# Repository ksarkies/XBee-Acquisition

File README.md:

XBee Data Acquisition
---------------------

This project develops a remote data collection board, primarily aimed at a
specific water flow meter. The board communicates collected counts of optical
transitions from a rotating slotted wheel, over an XBee network to a master
processing point. The remote unit includes a bootloader for remote upload of
new firmware.

The challenge with this project is to reduce power consumption to a minimum
to extend the life of the batteries, which may be difficult to access for
recharge in practice.

In addition to the board design and firmware, a number of tools are provided
to manage the network and collect data using Linux based hardware. These include
an acquisition coordination process that is intended to run on a small headless
Linux box such as a Raspberry Pi or BeagleBone. This manages the network and
connects to a user interface program running either on the same machine or
at another location. It uses a TCP/IP sockets interface that will allow remote
connections over the Internet.

A number of test and debug firmwares are available as well as schematics for
prototyping boards used as test nodes.

Subdirectories:

* **Documentation**:           A set of documents relevant to design and implementation.

* **gEDA-XBee-Test**:          Schematics for prototype boards for testing purposes.

* **Kicad-Main**:              Schematic and PCB for watermeter unit main board.

* **Kicad-Mounts**:            Schematic and PCB for XBee and LED mount boards.

* **watermeter-test**:         Firmware for the remote unit ATTiny481, in C, for use
 with flow bench testing over a serial interface. XBee is not used.

* **XBee-acqcontrol**:         Control software for the coordinator; in C++.

* **XBee-bootloader-M168**:    Bootloader for a remote unit with ATMega168.

* **XBee-experimental-T4313**: Bootloader for a remote unit with ATTiny4313.

* **XBee-firmware**:           Firmware for the remote unit ATTiny481, in C.

* **XBee-firmware-NARTOS**:    Firmware for remote unit ATTiny481 using the NARTOS
scheduler.

* **XBee-GUI**:                Linux PC based GUI for network control; C++ and QT.

* **XBee-node-example-M168**:  Example to send dummy message via XBee for testing.

* **XBee-utility**:            Some tools for direct interaction with XBee over a
serial interface.

K. Sarkies
29 January 2016

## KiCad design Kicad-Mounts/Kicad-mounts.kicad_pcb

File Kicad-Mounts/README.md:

XBee Data Acquisition XBee/LED Mountings
----------------------------------------

Refer to [Kicad-setup](https://github.com/ksarkies/XBee-Acquisition/blob/master/Documentation/Kicad-Setup.md) in the Documentation directory for usage information.

TDB: At this time the PCB has missing footprints.

This board provides a mounting PCB for the LED and a mounting PCB for the XBee
with matching connector for right-angle mount to the main PCB.

An XBee footprint was taken from RF_OEM_PARTS.lib and footprints.mod in Ian
McInerney's library (https://github.com/imciner2/KiCad-Libraries)
The legacy footprint has been modified to the newer kicad_mod format and solder
mask has been added to the pads.

The LED mount provides for two LEDs VSMY2850 and SFH4056 reverse mounted (under
the board and facing through a cutout) and a top mounted LED SFH4258.

Other symbols and footprints are provided by KiCad developers.

27 November 2014: Flip XBee over, adjust XBee footprint, reduce size the of the
                  two boards, interchange Rx and Tx.

A separate regulated supply was added to provide 3.3V power for the XBee as the
XBee can pull a relatively heavy current pulse on transmission.

K. Sarkies
19 February 2016

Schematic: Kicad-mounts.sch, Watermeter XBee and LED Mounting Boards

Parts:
C1: 0.47uF; SMD-0603_c
C2: 0.1uF; SMD-0603_c
C3: 10uF; SMD-1206_Pol
D1: SFH4056
P3: CONN_6X2; pin_header_2mm_2x6
P6: CONN_3; SIL-3
U2: TPS77033; SOT-23-5

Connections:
/Association: P3.10; also elsewhere on the board
/Bootloader: P3.3; also elsewhere on the board
/Commissioning: P3.1; also elsewhere on the board
/On/Sleep: P3.9; also elsewhere on the board
/Reset: P3.5; also elsewhere on the board
/Rx: P3.7; also elsewhere on the board
/Sleep_Rq: P3.8; also elsewhere on the board
/Tx: P3.12; also elsewhere on the board
/V3: C2.1, C3.1, U2.5 (OUT); also elsewhere on the board
/VBatt: P3.4; also elsewhere on the board
/XBee-Reset: P3.6; also elsewhere on the board
GND: C1.2, C2.2, C3.2, P3.11, U2.2 (GND), U2.3 (~EN~); also elsewhere on the board
unnamed: D1.1, P6.2, P6.3
unnamed: D1.2, P6.1
VCC: C1.1, P3.2, U2.1 (IN)

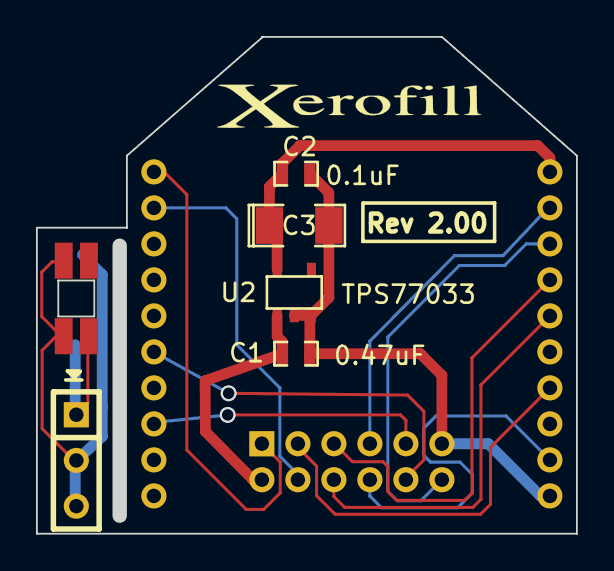
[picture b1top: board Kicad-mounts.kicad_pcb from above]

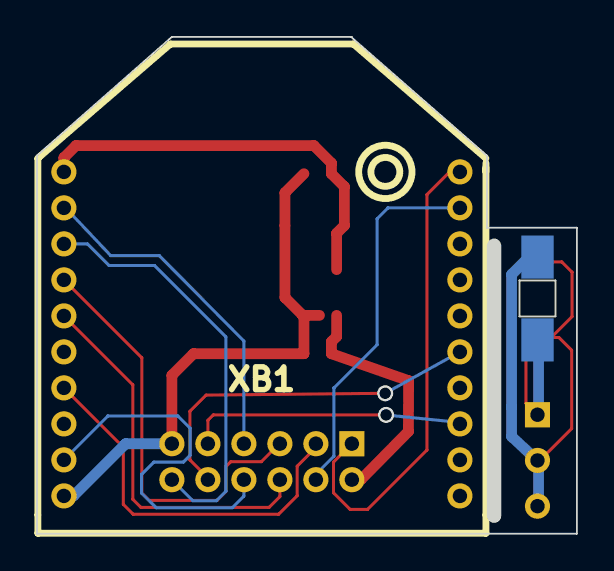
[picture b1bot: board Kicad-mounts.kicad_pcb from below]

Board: 2 copper layers, 30.0 x 27.6 mm, 8 parts (2 on the bottom side), 15 nets.

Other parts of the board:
XB1: XBEE; XBee

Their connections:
/Association: XB1.15; also elsewhere on the board
/Bootloader: XB1.7; also elsewhere on the board
/Commissioning: XB1.20; also elsewhere on the board
/On/Sleep: XB1.13; also elsewhere on the board
/Reset: XB1.4; also elsewhere on the board
/Rx: XB1.2; also elsewhere on the board
/Sleep_Rq: XB1.9; also elsewhere on the board
/Tx: XB1.3; also elsewhere on the board
/V3: XB1.1; also elsewhere on the board
/VBatt: XB1.19; also elsewhere on the board
/XBee-Reset: XB1.5; also elsewhere on the board
GND: XB1.10; also elsewhere on the board

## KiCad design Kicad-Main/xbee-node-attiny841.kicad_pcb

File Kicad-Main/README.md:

XBee Data Acquisition PCB
-------------------------

Refer to [Kicad-setup](https://github.com/ksarkies/XBee-Acquisition/blob/master/Documentation/Kicad-Setup.md) in the Documentation directory for usage information.

PCB for a remote unit, including XBee with battery monitor and photodiode
counter. A major requirement for this circuit is ultra-low power to allow the
selected batteries to last for over a year.

The PCB is intended to fit inside a cylindrical watermeter with the batteries.
Due to space constraints the XBee is mounted on a separate board that sits at
right angles to the PCB. The XBee connects to an external aerial through an RF
cable. For measurement of battery voltage, a switched divider circuit is
provided for the case that the batteries provide a higher voltage than the
circuit power supply (which is sourced via a 3.3V voltage regulator). The LED is
mounted on a separate board that will straddle an interrupter wheel for counting
revolutions of the meter.

The board has a 12-pin debug connector for testing purposes:

1. Battery power or board power (if a battery is present take extreme care not
to short or connect any other power source).
2. Count signal from board comparator.
3. Reset for microcontroller.
4. MOSI microcontroller programming pin.
5. SCK microcontroller programming pin.
6. MISO microcontroller programming pin.
7. Tx from microcontroller to XBee Rx (monitor this only unless XBee is removed).
8. Rx to microcontroller from XBee Tx (monitor this only unless XBee is removed).
9. Association Signal from XBee. Blinks at 2Hz when connected to the network.
10. On/Sleep (high if XBee is awake, low if asleep).
11. Commissioning input to XBee, requiring a pushbutton to ground.
12. Ground.

The microcontroller has the following I/O pin allocations:

* PA0 (in) XBee Asleep (inv)
* PA1 (out) Tx to XBee
* PA2 (in) Rx to XBee
* PA3 (out) Sleep Request
* PA4 (in) SCK
* PA5 (in) MISO
* PA6 (out) MOSI
* PA7 (out) Battery Monitor Control
* PB0 (in) Bootloader Enable
* PB1 (in) Board Digital Input
* PB2 (out) XBee Reset (inv)

The battery monitor voltage is passed directly to the XBee as the ATTiny841 has
insufficient pins.

The TPS77033 symbol from KB1LQC.lib at Rochester Institute of technology
(http://edge.rit.edu/edge/P13271/public/KiCad/Libraries).

A photodiode symbol was taken from
(http://vkoeppel.free.fr/files/diy/kicad_diy_libraries.zip)

Other symbols and footprints are custom or are provided by KiCad developers.

The provided Photodiode.pretty footprint library should contain all necessary
footprints. Copy any legacy footprints into the modules directory, and any
external footprints into Photodiode.pretty to avoid problems of obsolescence. In
CvPcb go to "Library Tables", then select the tab "Project Specific Libraries".
Append a new entry, add the library path (including the name of the .mod file),
choosing "Legacy" for the plugin type. The nickname will then appear in the main
listing of CvPcb and the library footprints should appear. If a mistake is made,
no footprints will show, but no error message will be given until CvPcb is
restarted.

A custom footprint S1133 is provided for the S1133 photodiode. This has a
truncated circular form 8mm diameter with 6mm across the truncation, and through
hole pins. In CvPcb append a new KiCad entry and add the library path to the
.pretty directory (not the file, which is a single footprint). Also included
are some 2mm pin spacing header footprints.

The production version of the board has a custom footprint for the debug
connector to allow the option of using an SMD form. Also the photodiode is now
a BPW34 which can be either SMD or through hole mounted below the board, or a
reverse form mounted on top of the board over the square hole. The latter choice
avoids possible interference with mechanical parts in the space under the board.

The [node test firmware](https://github.com/ksarkies/XBee-Acquisition/tree/master/Development/XBee-node-test) is provided for test transmissions.

The [firmware](https://github.com/ksarkies/XBee-Acquisition/tree/master/XBee-firmware) is provided for full protocol transmissions.

Firmware must be compiled for MCU=attiny841 or whichever processor is used.

The firmware README provides instructions for setting up the XBee configuration.

* 27 November 2014: Add missing ground points. Correct error in battery voltage
  circuit.
* 24 February 2016: Changed position of connectors to avoid housing structures.
* 11 April 2016: Production version with additional XBee signals brought out to
  the debug connector which is now 12 pin.
* 12 February 2017: Corrections to the battery monitor circuit.

K. Sarkies
11 April 2016

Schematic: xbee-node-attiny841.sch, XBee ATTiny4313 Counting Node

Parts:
C1, C2, C6, C7, C8, C9: 0.1uF; SM0603_Capa
C3: 10uF; SM1206POL
C4: 0.47uF; SM0603_Capa
D1: SFH4056; LED-Mount
D2: BPW-34 S (E9087); BPW34
L1: 100nH; R_0805
P2: XBee Adaptor; pin_header_2mm_2x6
P3: Debug Adaptor; pin_smd_header_2mm_2x6
P7, P8, P9, P10, P11: CONN_1; SIL-1
P12, P13, P14, P15, P16, P17, P18, P19, P20: CONN_1; THROUGHVIA
Q1: BSS84; SOT23GDS
Q2: MMBT3904; SOT23EBC
Q3: 2N7002; SOT23GDS
R1, R6: 10K; SM0603_Resistor
R2: 33K; SM0603_Resistor
R3: 270K; SM0603_Resistor
R4, R5, R9: 1M; SM0603_Resistor
R7: 15K; SM0603_Resistor
R8: 4.7K; SM0603_Resistor
U1: ATTINY841; ATTINY841-SSU
U2: MAX952ESA; SO8N
U3: TPS77033; SOT23-5

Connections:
/Association: P2.10, P3.9
/Battery: C4.1, P2.2, P3.1, P7.1, P8.1, P9.1, Q1.S, R6.1, U3.1 (IN)
/Bootloader: P2.3, U1.2 ((PCINT8/CLKI/XTAL1)PB0)
/Commissioning: P2.1, P3.12
/Count: P3.2, R4.2, U1.3 ((PCINT9/XTAL2)PB1), U2.7
/MISO: P3.6, U1.8 ((PCINT5/DO/MISO/OC1B/ADC5)PA5)
/MOSI: P3.4, U1.7 ((PCINT6/SDA/DI/MOSI/OC1A/ADC6)PA6)
/On/Sleep: P2.9, P3.10, U1.13 ((PCINT0/AREF/ADC0)PA0)
/PowerControl: Q3.G, R9.2, U1.6 ((PCINT7/ICP/OC0B/ADC7)PA7)
/Reset: C1.1, P2.5, P3.3, R1.1, U1.4 ((PCINT11/dW/~RESET~)PB3)
/Rx: P2.7, P3.8, U1.11 ((PCINT2/AIN1/ADC2)PA2)
/SCK: P3.5, U1.9 ((PCINT4/USCK/SCL/T1/ADC4)PA4)
/Sleep-Rq: P2.8, R5.2, U1.10 ((PCINT3/T0/ADC3)PA3)
/Tx: P2.12, P3.7, U1.12 ((PCINT1/AIN0/ADC1)PA1)
/VBatt: P2.4, R7.2, R8.1
/VDDA: C6.1, C9.1, D2.2 (K), L1.1, R2.1, R3.1, U2.8 (V+)
/Xbee-Reset: P2.6, U1.5 ((PCINT10/CKOUT/OC0A/INT0)PB2)
GND: C1.2, C2.2, C3.2, C4.2, C6.2, C7.2, C8.2, C9.2, D1.2 (K), P2.11, P3.11, P10.1, P11.1, P12.1, P13.1, P14.1, P15.1, P16.1, P17.1, P18.1, P19.1, P20.1, Q2.1 (E), Q3.S, R5.1, R8.2, R9.1, U1.14 (GND), U2.2 (-), U2.3 (+), U2.4 (V-), U3.2 (GND), U3.3 (~EN~); also elsewhere on the board
unnamed: D1.1 (A), R2.2
unnamed: D2.1 (A), Q2.2 (B)
unnamed: Q1.D, R7.1
unnamed: Q1.G, Q3.D, R6.2
unnamed: Q2.3 (C), R3.2, R4.1, U2.5 (+)
VDD: C2.1, C3.1, C7.1, C8.1, L1.2, R1.2, U1.1 (VCC), U3.5 (OUT)

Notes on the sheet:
Battery Connections
Vias
XBee Connectors
Debug Connector

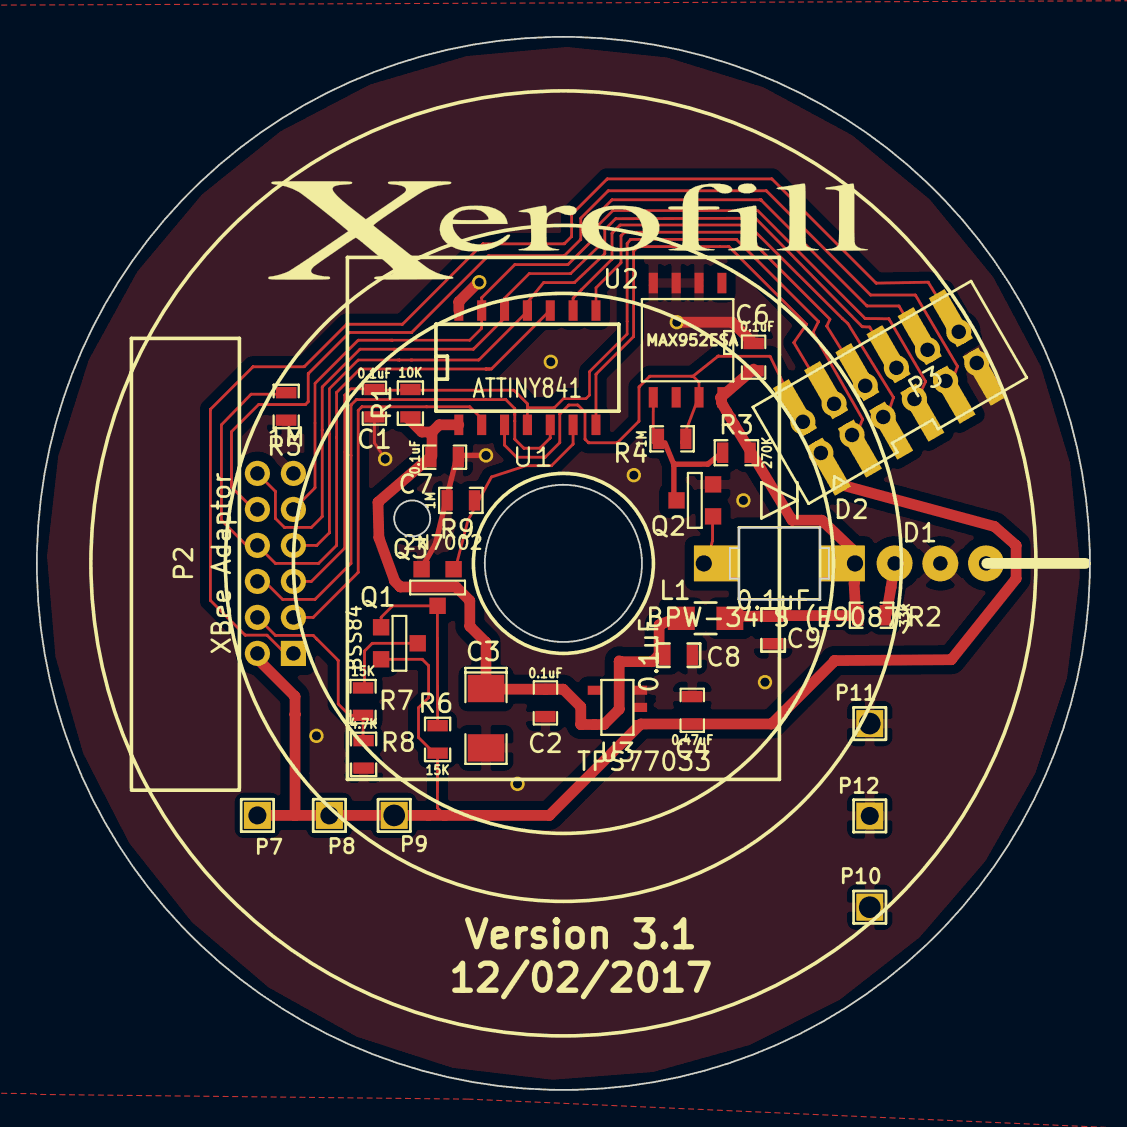
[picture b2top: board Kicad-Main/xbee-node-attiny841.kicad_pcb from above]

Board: 2 copper layers, 58.5 x 58.5 mm, 44 parts (0 on the bottom side), 24 nets.

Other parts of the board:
P12#2: CONN_1; THROUGHVIA
Ref**: Val**; THROUGHVIA

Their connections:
GND: P12#2.1, Ref**.1; also elsewhere on the board

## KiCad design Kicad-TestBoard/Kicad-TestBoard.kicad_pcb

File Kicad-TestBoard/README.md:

XBee Data Acquisition TestBoard
-------------------------------

This board is for use with the watermeter assembly. It provides power, an
interface to an AVR programmer, and a serial interface to an external PC.
LEDs are provided for association indication, on/sleep and commissioning
signals from the XBee. A reset switch for the AVR is provided.

There are pins for a CRO to view the count signal from the assembly.

Jumpers are provided as follows:

* Disconnect external serial line. This **must** be left open when the XBee is
present in the watermeter assembly otherwise both serial sources are
mutually interfering and the XBee could be damaged.

* Disconnect power to watermeter assembly. This **must** be left open when the
watermeter assembly has an on-board battery. With Lithium batteries there is a
strong chance of explosion or fire if an external voltage source is connected.

K. Sarkies
19 January 2017

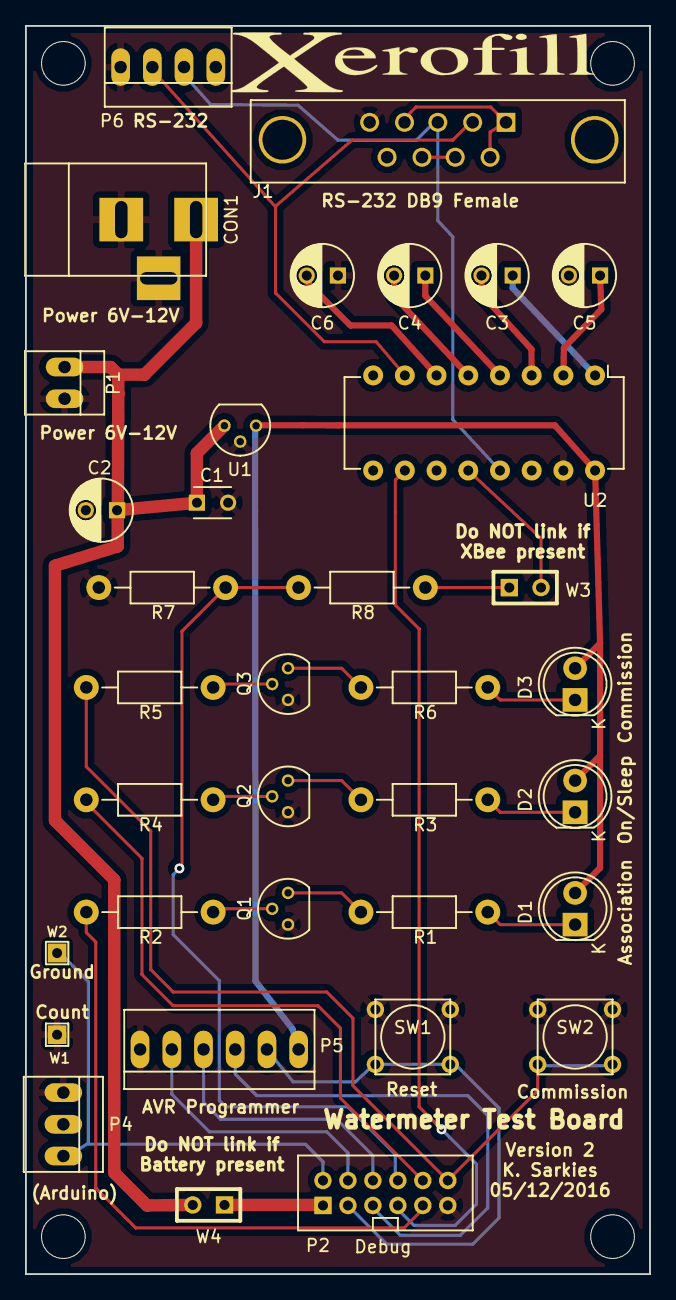
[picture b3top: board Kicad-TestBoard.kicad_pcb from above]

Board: 2 copper layers, 50.0 x 100.0 mm, 35 parts (0 on the bottom side), 35 nets.

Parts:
C1: 0.1uF; C_Disc_D3_P2.5
C2: 10uF; C_Radial_D5_L11_P2.5
C3, C4, C5, C6: 1uF; C_Radial_D5_L11_P2.5
CON1: Power 6V-12V; BARREL_JACK
D1: Yellow LED; LED-5MM
D2: Green LED; LED-5MM
D3: Red LED; LED-5MM
J1: DB9 RS-232 Female; DB9FD
P1: Power 6V-12V; PINHEAD1-2
P2: Debug; pin_header_2mm_2x6_shrouded
P4: Arduino; PINHEAD1-3
P5: AVR Programmer; PINHEAD1-6
P6: RS-232; PINHEAD1-4
Q1: Association; TO-92_Molded_Narrow
Q2: On_Sleep; TO-92_Molded_Narrow
Q3: Commissioning; TO-92_Molded_Narrow
R1, R3, R6, R8: 470; Resistor_Horizontal_RM10mm
R2, R4, R5: 10K; Resistor_Horizontal_RM10mm
R7: 1K; Resistor_Horizontal_RM10mm
SW1: Reset; SW_PUSH_TINY
SW2: Commissioning; SW_PUSH_TINY
U1: 78L05; TO-92_78L05
U2: MAX232; DIP-16_W7.62mm
W1, W2: TEST_1P; SIL-1
W3, W4: Jumper; SIL-2

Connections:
/Battery: P2.1, W4.1
/Commissioning: P2.12, R5.2, SW2.2
/Count: P2.2, P4.3, W2.1
/MISO: P2.6, P5.3
/MOSI: P2.4, P5.2
/On_Sleep: P2.10, R4.2
/Reset: P2.3, P5.5, SW1.2
/Rx: P2.8, R7.1, R8.2
/SCK: P2.5, P5.4
/Tx: P2.7, U2.10
Earth: C1.2, C2.2, C5.2, C6.1, CON1.2, CON1.3, J1.5, P1.2, P2.11, P4.1, P5.1, P6.4, Q1.1, Q2.1, Q3.1, R7.2, SW1.1, SW2.1, U1.GND, U2.15, W1.1
unnamed: C1.1, C2.1, CON1.1, P1.1, U1.VI, W4.2
unnamed: C3.1, U2.1
unnamed: C3.2, U2.3
unnamed: C4.1, U2.4
unnamed: C4.2, U2.5
unnamed: C5.1, U2.2
unnamed: C6.2, U2.6
unnamed: D1.1, R1.1
unnamed: D2.1, R3.1
unnamed: D3.1, R6.1
unnamed: J1.1, J1.4, J1.6
unnamed: J1.2, P6.3, U2.7
unnamed: J1.3, P6.2, U2.13
unnamed: J1.7, J1.8
unnamed: P2.9, R2.2
unnamed: Q1.2, R2.1
unnamed: Q1.3, R1.2
unnamed: Q2.2, R4.1
unnamed: Q2.3, R3.2
unnamed: Q3.2, R5.1
unnamed: Q3.3, R6.2
unnamed: R8.1, W3.1
unnamed: U2.12, W3.2
VCC: D1.2, D2.2, D3.2, P5.6, U1.VO, U2.16

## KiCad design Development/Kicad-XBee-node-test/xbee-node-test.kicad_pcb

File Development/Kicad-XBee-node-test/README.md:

XBee Node Test Board PCB
------------------------

This is a small test board PCB.

This includes an XBee with ATMega48 and with an analogue battery monitor,
digital counter input and a second analogue input. It takes an input 5-14V power
and produces 3.3V power for the electronics.

The microcontroller has the following I/O pin allocations:

* PB2 (in) Bootloader Enable taken from XBee DIO11 pin..
* PB3 (out) Programming SPI interface MOSI.
* PB4 (in) Programming SPI interface MISO.
* PB5 (in) Programming SPI interface SCK.
* PC0 (in) Board Analogue Input also taken to XBee AD2 pin.
* PC1 (in) Battery Monitor Analogue Input also taken to XBee AD1 pin.
* PC3 (out) Debug Signal LED.
* PC4 (out) Microcontroller Activity LED.
* PC5 (out) Battery Monitor Control.
* PD2 (in) taken from XBee CTS pin.
* PD3 (out) taken to XBee RTS pin.
* PD4 (in) Board Digital Input.
* PD5 (out) XBee Sleep Request.
* PD6 (in) XBee On/Sleep.
* PD7 (out) XBee Reset (inv) taken to the XBee reset pin.
* Microcontroller Reset taken from XBee DIO12 pin.

Four LEDs are provided:
* Red       Power.
* Green     PC4 Microcontroller Activity (test port) from ATMega48.
* Blue      Debug Signal.
* Yellow    Association status from XBee.

The [node test firmware](https://github.com/ksarkies/XBee-Acquisition/tree/master/Development/XBee-node-test) is provided for test transmissions.

The [firmware](https://github.com/ksarkies/XBee-Acquisition/tree/master/XBee-firmware) is provided for full protocol transmissions.

Firmware must be compiled for MCU=atmega48 or whichever processor is used.

The firmware README provides instructions for setting up the XBee configuration.

K. Sarkies
2 March 2017

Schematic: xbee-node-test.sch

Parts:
C1, C2, C3, C4, C5: 0.1uF; SM0603_Capa
C6, C7: 10uF; SM1206POL
C8: 0.47uF; SM0603_Capa
D1: LM336-2.5V; TO-92_LM336
D2: Test; LED-5MM
D3, D5: 1N4148; D_0603
D4: Associate; LED-5MM
D6: Debug; LED-5MM
D7: Power; LED-5MM
D8: CUS520; D_SOD-323_HandSoldering
IC1: ATMEGA48-P; DIP-28
L1, L2: 100nH; R_0805
P1: Program; PINHEAD1-6
P2: Power 3.7V-12V; PINHEAD1-2
P3: Analogue; PINHEAD1-2
P4: Count; PINHEAD1-2
P5: VRef; SIL-1
P6: GND; SIL-1
Q1: 2N7002; SOT23GDS
Q2: BSS84; SOT23GDS
R1, R9, R11: 10K; SM0603_Resistor
R2: 2.2K; SM0603_Resistor
R3, R4, R5, R6: 220; SM0603_Resistor
R7, R8, R14: 1M; SM0603_Resistor
R10: 1K; SM0603_Resistor
R12: 15K; SM0603_Resistor
R13: 4.7K; SM0603_Resistor
RV1: 100K; Potentiometer_Bourns_3362F
Reset1: Reset; SW_PUSH_TINY
SW2: Commissioning; SW_PUSH_TINY
U1: TPS77033; SOT23-5
W1, W2, W3: Jumper; SIL-2
XB1: XBEE; XBee

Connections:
/ARef: C2.1, D1.2 (+), D3.2 (A), IC1.21 (AREF), P5.1, R2.2
/AVcc: C4.1, IC1.20 (AVCC), L2.1
/Analogue: IC1.23 ((PCINT8/ADC0)PC0), R10.2, R14.1, XB1.18 (AD2/DIO2)
/Associate: W2.2, XB1.15 (AD5/DIO5)
/Battery: D8.2 (A), P2.1, Q2.S, R9.1
/Bootloader: IC1.16 ((PCINT2/OC1B/~SS~)PB2), XB1.7 (PWM1)
/CTS: IC1.4 ((PCINT18/INT0)PD2), XB1.12 (DIO7/~CTS~)
/Commissioning: SW2.1, XB1.20 (AD0/DIO0)
/Counter: IC1.6 ((PCINT20/XCK/T0)PD4), R11.2
/DEBUG: IC1.26 ((PCINT11/ADC3)PC3), R5.2
/MC_Reset: C1.1, IC1.1 ((PCINT14/~RESET~)PC6), P1.5, R1.2, Reset1.1, XB1.4 (D08)
/MISO: IC1.18 ((PCINT4/MISO)PB4), P1.3
/MOSI: IC1.17 ((PCINT3/OC2/MOSI)PB3), P1.2
/On_Sleep: IC1.11 ((PCINT21/OC0B/T1)PD5), XB1.13 (ON/~SLEEP~)
/RTS: IC1.5 ((PCINT19/OC2B/INT1)PD3), XB1.16 (~RTS~/AD6/DIO6)
/RxD: IC1.2 ((PCINT16/RXD)PD0), XB1.2 (DOUT)
/SCK: IC1.19 ((PCINT5/SCK)PB5), P1.4
/Sleep_RQ: IC1.12 ((PCINT22/OC0A/AIN0)PD6), R7.1, XB1.9 (~DI8~/DTR/SLEEP_RQ)
/TEST: IC1.27 ((PCINT12/SDA/ADC4)PC4), R3.2
/TxD: IC1.3 ((PCINT17/TXD)PD1), XB1.3 (DIN/~CONFIG)
/VBAT: IC1.24 ((PCINT9/ADC1)PC1), R12.2, R13.1, XB1.19 (AD1/DIO1)
/VBAT_CTL: IC1.28 ((PCINT13/SCL/ADC5)PC5), Q1.G, R8.1
/Vcc: C3.1, C5.1, IC1.7 (VCC), L1.1, P1.6, R1.1, W1.1, W3.2, XB1.1 (VCC)
/XBee_Reset: IC1.13 ((PCINT23/AIN1)PD7), XB1.5 (~RESET)
GND: C1.2, C2.2, C3.2, C4.2, C5.2, C6.2, C7.2, C8.2, D1.3 (-), D2.1 (K), D4.1 (K), D5.1 (K), D6.1 (K), D7.1 (K), IC1.8 (GND), IC1.22 (GND), P1.1, P2.2, P3.2, P4.2, P6.1, Q1.S, R7.2, R8.2, R13.2, R14.2, Reset1.2, SW2.2, U1.2 (GND), U1.3 (~EN~), XB1.10 (GND)
unnamed: C6.1, L1.2, L2.2, U1.5 (OUT)
unnamed: C7.1, C8.1, D8.1 (K), U1.1 (IN)
unnamed: D1.1 (ADJ), RV1.2
unnamed: D2.2 (A), R3.1
unnamed: D3.1 (K), RV1.3
unnamed: D4.2 (A), R4.1
unnamed: D5.2 (A), RV1.1
unnamed: D6.2 (A), R5.1
unnamed: D7.2 (A), R6.1
unnamed: P3.1, R10.1
unnamed: P4.1, R11.1
unnamed: Q1.D, Q2.G, R9.2
unnamed: Q2.D, R12.1
unnamed: R2.1, W1.2
unnamed: R4.2, W2.1
unnamed: R6.2, W3.1

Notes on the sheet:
XBee Node test Board
31/01/2017

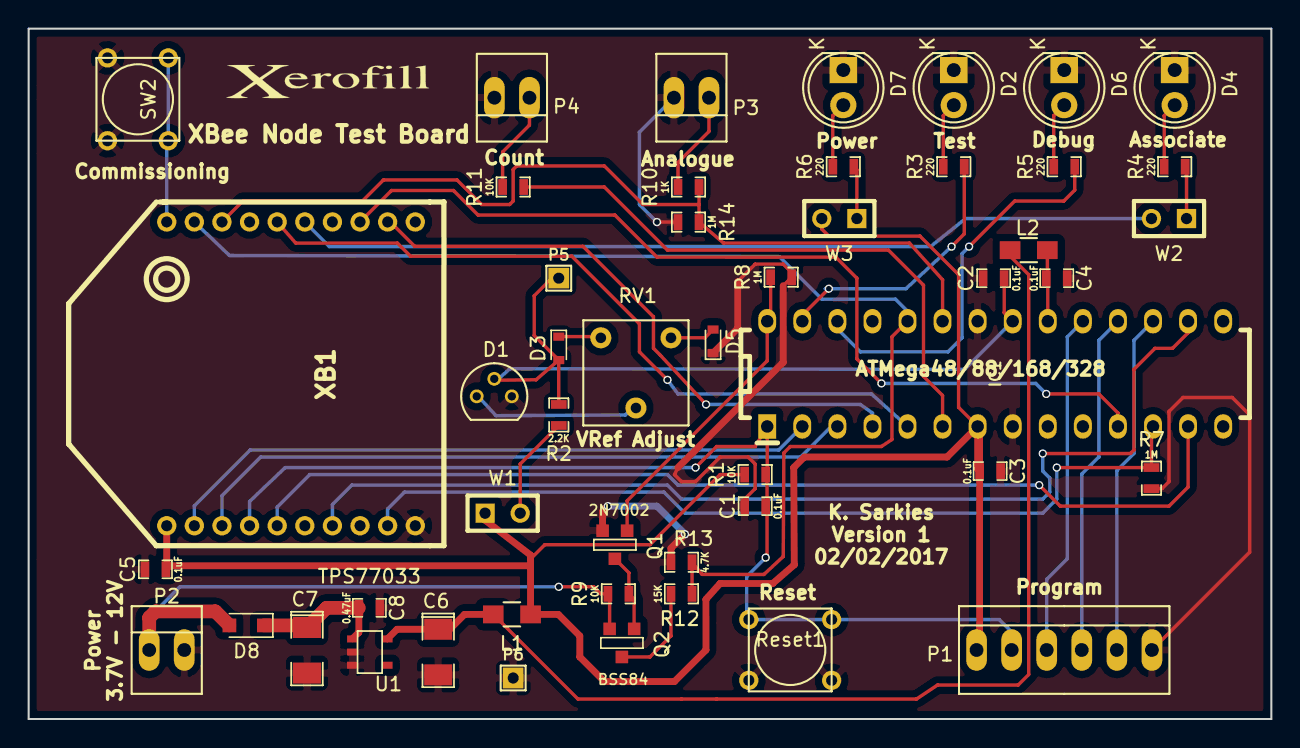
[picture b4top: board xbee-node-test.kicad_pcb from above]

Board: 2 copper layers, 90.0 x 50.0 mm, 49 parts (0 on the bottom side), 41 nets.

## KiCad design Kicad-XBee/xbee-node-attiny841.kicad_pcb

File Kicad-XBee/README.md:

XBee Data Acquisition PCB
-------------------------

PCB for remote unit, including XBee with battery monitor and photodiode
counter. A major requirement for this circuit is ultra-low power to allow the
batteries to last for over a year.

The PCB is intended to fit inside a cylindrical watermeter along with batteries.
Due to space constraints the XBee is mounted on a separate board that sits at
right angles to the PCB. The XBee connects to an external aerial through an RF
cable. For measurement of battery voltage, a switched divider circuit is
provided for the case that the batteries provide a higher voltage than the
circuit power supply which is sourced via a voltage regulator). The LED is
mounted on a separate board that will straddle an interrupter wheel for counting
revolutions of the meter.

XBee and 5x2 connector symbol and footprint is taken from Ian McInerney:
https://github.com/imciner2/KiCad-Libraries RF_OEM_PARTS.lib and footprints.mod

TPS77033 symbol from Rochester Institute of technology:
http://edge.rit.edu/edge/P13271/public/KiCad/Libraries KB1LQC.lib and KB1LQC.mod

The latter is a legacy footprint. Place the file into the modules directory. In
CvPcb go to "Library Tables", then select the tab "Project Specific Libraries".
Append a new entry, add the library path (including the name of the .mod file),
choosing "Legacy" for the plugin type. The nickname will then appear in the main
listing of CvPcb and the library footprints should appear. If a mistake is made,
no footprints will show, but no error message will be given until CvPcb is
restarted.

A custom footprint S1133 is provided for the photodiode. This actually has a
truncated circular form 8mm diameter with 6mm across the truncation, and through
hole pins. In CvPcb append a new KiCad entry and add the library path to the
.pretty directory (not the file, which is a single footprint). Also included
are some 2mm pin spacing header footprints.

K. Sarkies
9 August 2014

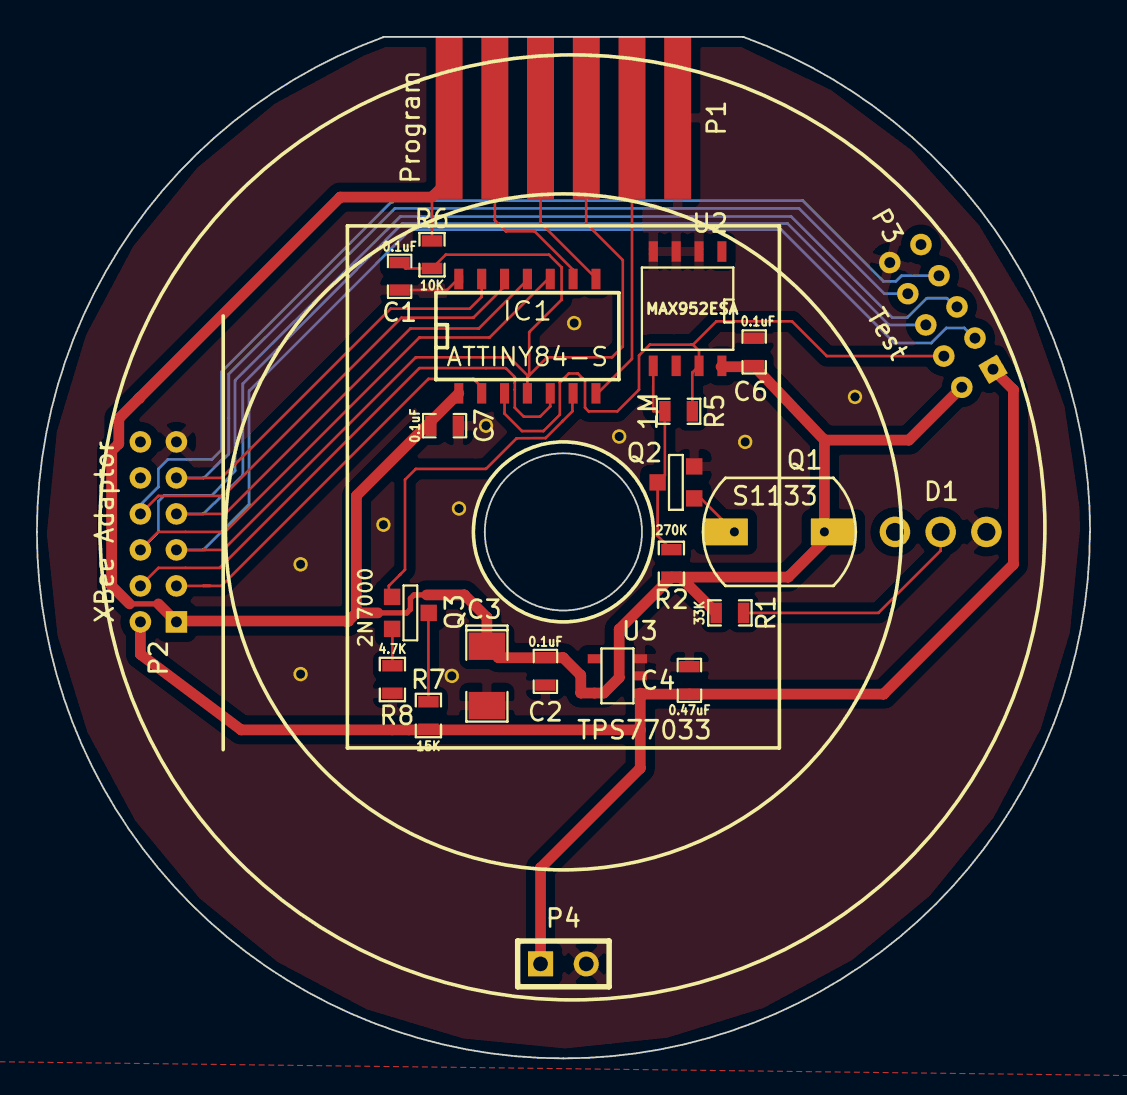
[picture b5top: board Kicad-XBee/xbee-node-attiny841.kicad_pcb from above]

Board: 2 copper layers, 58.5 x 56.8 mm, 33 parts (0 on the bottom side), 20 nets.

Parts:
C1, C2, C6, C7: 0.1uF; SM0603_Capa
C3: 10uF; SM1206POL
C4: 0.47uF; SM0603_Capa
D1: APD3224ZGC-F01; LED-Mount
IC1: ATTINY84-S; SO14N
P1: Program; edge_conn_6_pin
P2: XBee Adaptor; pin_header_2mm_2x6
P3: Test; pin_header_2mm_2x5
P4: Battery; SIL-2
Q1: S1133; S1133TH
Q2: S9014; SOT23EBC
Q3: 2N7000; SOT23GDS
R1: 33K; SM0603_Resistor
R2: 270K; SM0603_Resistor
R5: 1M; SM0603_Resistor
R6: 10K; SM0603_Resistor
R7: 15K; SM0603_Resistor
R8: 4.7K; SM0603_Resistor
Ref**: Val**; THROUGHVIA
Ref**#2, Ref**#3, Ref**#4, Ref**#5, Ref**#6, Ref**#7, Ref**#8, Ref**#9, Ref**#10: Val**; THROUGHVIA
U2: MAX952ESA; SO8N
U3: TPS77033; SOT23-5

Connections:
/Bootloader: IC1.2, P2.3
/Count: IC1.3, P3.4, R5.2, U2.7
/MISO: IC1.8, P1.4
/MOSI: IC1.7, P1.2
/On/Sleep: IC1.13, P2.9, P3.8
/Reset: C1.1, IC1.4, P1.3, P2.5, P3.3, R6.1
/Rx: IC1.11, P2.7, P3.6
/SCK: IC1.9, P1.5
/Sleep-Rq: IC1.10, P2.6, P3.5
/Tx: IC1.12, P2.8, P3.7
/VBatt: C4.1, P2.2, P3.1, P4.1, R7.1, U3.1
/Xbee-Reset: IC1.5, P2.4
GND: C1.2, C2.2, C3.2, C4.2, C6.2, C7.2, D1.1, IC1.14, P1.1, P2.11, P3.10, P4.2, Q2.1, R8.2, Ref**.1, Ref**#2.1, Ref**#3.1, Ref**#4.1, Ref**#5.1, Ref**#6.1, Ref**#7.1, Ref**#8.1, Ref**#9.1, Ref**#10.1, U2.2, U2.3, U2.4, U3.2, U3.3
unnamed: D1.2, R1.2
unnamed: IC1.6, Q3.G
unnamed: Q1.1, Q2.2
unnamed: Q2.3, R2.2, R5.1, U2.5
unnamed: Q3.D, R7.2
unnamed: Q3.S, R8.1
VDD: C2.1, C3.1, C6.1, C7.1, IC1.1, P1.6, P2.1, P3.2, Q1.3, R1.1, R2.1, R6.2, U2.8, U3.5

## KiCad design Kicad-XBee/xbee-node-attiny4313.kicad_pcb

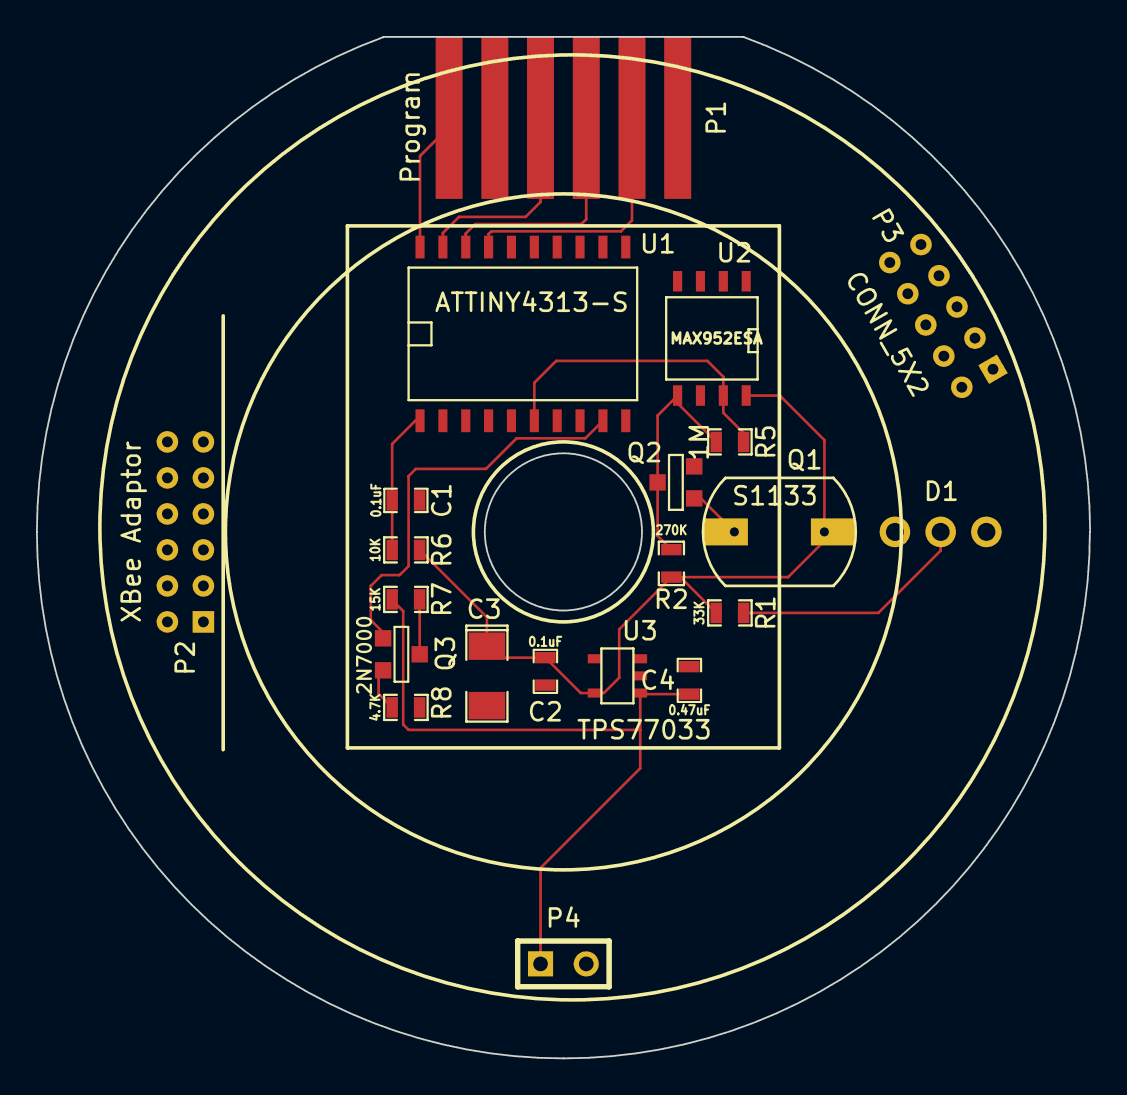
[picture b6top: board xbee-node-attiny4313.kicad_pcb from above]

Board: 2 copper layers, 58.5 x 56.8 mm, 21 parts (0 on the bottom side), 22 nets.

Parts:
C1, C2: 0.1uF; SM0603_Capa
C3: 10uF; SM1206POL
C4: 0.47uF; SM0603_Capa
D1: APD3224ZGC-F01; LED-Mount
P1: Program; edge_conn_6_pin
P2: XBee Adaptor; pin_header_2mm_2x6
P3: CONN_5X2; pin_header_2mm_2x5
P4: Battery; SIL-2
Q1: S1133; S1133TH
Q2: S9014; SOT23EBC
Q3: 2N7000; SOT23GDS
R1: 33K; SM0603_Resistor
R2: 270K; SM0603_Resistor
R5: 1M; SM0603_Resistor
R6: 10K; SM0603_Resistor
R7: 15K; SM0603_Resistor
R8: 4.7K; SM0603_Resistor
U1: ATTINY4313-S; SO20L
U2: MAX952ESA; SO8N
U3: TPS77033; SOT23-5

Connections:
/Bootloader: P2.7, U1.16
/CTS: P2.4, U1.4
/On/Sleep: P2.8, P3.6, U1.13
/RTS: P2.6, U1.5
/Reset: C1.1, P1.5, P2.9, P3.7, R6.1, U1.1
/Rx: P2.3, P3.1, U1.2
/Sleep-Rq: P2.2, P3.2, U1.15
/Tx: P2.5, P3.3, U1.3
/VBatt: C4.1, P2.12, P3.10, P4.1, R7.1, U3.1
/Xbee-Reset: P2.10, P3.8, U1.14
GND: C1.2, C2.2, C3.2, C4.2, D1.1, P1.1, P2.11, P3.9, P4.2, Q2.1, R8.2, U1.10, U2.2, U2.3, U2.4, U3.2, U3.3
unnamed: D1.2, R1.2
unnamed: P1.2, U1.17
unnamed: P1.3, U1.18
unnamed: P1.4, U1.19
unnamed: P3.5, R5.2, U1.6, U2.7
unnamed: Q1.1, Q2.2
unnamed: Q2.3, R2.2, R5.1, U2.5
unnamed: Q3.D, R7.2
unnamed: Q3.G, U1.9
unnamed: Q3.S, R8.1
VDD: C2.1, C3.1, P1.6, P2.1, Q1.3, R1.1, R2.1, R6.2, U1.20, U2.8, U3.5

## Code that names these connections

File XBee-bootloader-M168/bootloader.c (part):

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One of the input pins on the microcontroller is tested and used as an
instruction to remain in the bootloader after a reset. This should be an XBee
output pin. After firmware update is complete the program may be entered by
simply removing the signal on this pin. While the bootloader is active, an
output pin on the microcontroller is used to force the XBee to remain awake.
This must be connected to the Sleep Request pin of the XBee.

This bootloader is written to the top of FLASH memory. It requires almost 2K
of space, and so is suited only to microcontrollers with 4K of memory or more.
The code supports microcontrollers a separate bootloader section. The fuses
must be set to jump to the bootloader on reset. If the bootloader pin is not
active the bootloader will then jump directly to the application code at
location zero, and also after firmware has been uploaded.

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{
    uint8_t ch;

/* Cause jump to app if bootloader pin is inactive.
MCU_TYPE 1 needs this as it has a separate bootloader section. */
/* Pointer to app start. */
    void (*jumpToApp)( void ) = 0x0000;

/* Test for the bootloader pin pulled high, then jump directly to the
application. If this is not used, the J instruction will provide the jump.*/
#if AUTO_ENTER_APP == 1
    if ((inb(PROG_PORT) & _BV(PROG_PIN)) > 0)
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void setXbeeWake(void)
{
#if XBEE_STAY_AWAKE == 1
    sbi(SLEEP_RQ_PORT_DIR,SLEEP_RQ_PIN);
    cbi(SLEEP_RQ_PORT,SLEEP_RQ_PIN);
#endif
}
/*-----------------------------------------------------------------------------*/
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    UART_CONTROL_REG |= _BV(ENABLE_RECEIVER_BIT) |
                        _BV(ENABLE_TRANSMITTER_BIT);    // enable receive and transmit 
#ifdef USE_HARDWARE_FLOW
    cbi(UART_CTS_PORT_DIR,UART_CTS_PIN);                // Set flow control pins CTS input
    sbi(UART_RTS_PORT_DIR,UART_RTS_PIN);                // RTS output
    cbi(UART_RTS_PORT,UART_RTS_PIN);                    // RTS cleared to enable
#endif
}

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unsigned char getch(void)
{
#ifdef USE_HARDWARE_FLOW
    cbi(UART_RTS_PORT,UART_RTS_PIN);                        // Enable RTS
#endif
    while (!(UART_STATUS_REG & _BV(RECEIVE_COMPLETE_BIT)));
#ifdef USE_HARDWARE_FLOW
    sbi(UART_RTS_PORT,UART_RTS_PIN);                        // Disable RTS
#endif
    return UART_DATA_REG;
}
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
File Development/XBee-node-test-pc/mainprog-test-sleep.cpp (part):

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    wdtCounter = 0;

/* Initialise process counter */
    counter = 0;

    transmitMessage = false;
}
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
/* Read the battery voltage from the XBee. */
#ifdef VBATCON_PIN
            sbi(VBATCON_PORT_DIR,VBATCON_PIN);  /* Turn on battery measurement */
#endif
            uint8_t data[12];
            int8_t dataLength = readXBeeIO(data);
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/****************************************************************************/
/** @brief Sleep the XBee

This sets the Sleep_RQ pin high. If the XBee is in pin hibernate mode, it will
hold it asleep indefinitely until the Sleep_RQ pin is set low again. If the XBee
is in cyclic/pin wake mode, this will have no effect.

The XBee may take some time before sleeping, however no operations are dependent
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/****************************************************************************/
/** @brief Wake the XBee

If the XBee is asleep, toggle the Sleep_RQ pin high then low. If the XBee is in
pin hibernate mode, this will hold it awake until the Sleep_RQ pin is set high
again or until the XBee wake period has expired. This is the mode the XBee
should be using in this application. Set the XBee wake period sufficiently long
if better control of wake time is desired.
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
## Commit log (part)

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2014-07-07 Initial commit of project. Work needs to be done to fix build dependency problems
2014-07-07 Correct a few bugs preventing build. Update Readme files. Remove redundant directory.
2014-07-19 Change all to APACHE licence Change directories around. Remove irrelevant directories and change names of others. Develop firmware for node.
2014-07-24 Addition of Kicad schematic for node
2014-07-27 More work on Kicad PCB. Remove LED (which will be on a separate board) and replace with connector. Add most footprints. Photodiode will need a custom footprint to be added later.
2014-08-06 Change to the ATTiny841 as the ATTiny4313 is 2.5mm high, and will interfere with the slotted disk. Completed layout but ground planes and power track widths still to be fixed.
2014-08-07 Complete Kicad PCB
2014-08-09 Start work on GUI to allow application specific window and code.
2014-08-31 Modification of boards after checking. Addition of other LED types to LED mount board.
2014-09-19 Update readme for the firmware Minor doc changes to the gui
2014-09-20 Bootloader needs hardware flow control. Adapted other files to put core hardware defines into the defines header.
2014-09-22 Generalize and revert back to single directory in firmware, bootloader and example, with makefile to pass on microcontroller type.
2014-09-23 Change Xbee send function to reduce stack usage for ATTiny4313 limited RAM
2014-09-24 Move define headers and serial libs to a use a common set. Add code for type 2 (AVRs without a bootloader section) to test bootloader pin and jump to the bootloader address. Change optimization level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
2014-09-24 Attempt to get example working for ATTiny4313. OK when first programmed. Corrected some old settings in the defines header. goto statement used wrong address. Go back to the function call. Still has 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
2014-09-25 Modify the ATMega168 example to work with the associated bootloader. Only works for -O1, not even -O0.
2014-09-25 Remove ATTiny4313 node example
2014-10-31 Update PCBs
2014-11-12 Modify the command line call to pass parameters for results directory, serial port and baudrate.
2014-11-14 Update readme on experimental firmware. NOTE this firmware is to be investigated to use TinySafeBoot
2014-11-18 XBee firmware testing. AVR sleep, wake with Watchdog interrupt. Sends a message from ISR, then sends a count message.
2014-11-26 Firmware now counts in the ISRs. Remains awake to receive a return message. Remains awake as long as counts are changing to avoid rapid sleep/wake cycles.
2014-11-29 Correction of some bugs in firmware to eliminate all but data packets. Update of some documentation in readme and serial.c
2014-12-01 Update firmware and controller for a different protocol in which the remote sends the checksum and the controller either accepts or rejects it.
2014-12-04 Xbee-acqcontrol add recording of verified count data. Need to generalise this later to other data types.
2014-12-12 Firmware: attempt to deal with more error conditions. However the complexity is too great and focus will move to a NARTOS implementation
2014-12-12 Firmware: put aside working copy and rewrite to include all error responses.
2014-12-14 Update main board to filter analogue power runs and shield input signals.
2014-12-14 Firmware increase debounce to 100us to wipe out transmitter interference (measured at 50us). This relies on the interference to remain short.
2014-12-18 GUI mods to fix operation of multiple xbee-control windows and fix segfault for local coordinator window.
2014-12-20 Main board: add a regulator for the XBee power only, plus capacitor.
2015-02-28 Test firmware to send csv counter data to an external acquisition unit.
2016-01-14 Photos of meter board and testbench I/F board
2016-02-18 Setup of KiCad projects to point to local libraries in repository. Corrections to mounts schematic.
2016-02-22 Move some components away from centre to leave room for a shaft housing.
2016-02-25 Change mount board to rotate XBee sideways and keep dual row connector only
2016-03-01 Update to documentation mounts PCB images
2016-03-02 GUI Update to QT5. Revert xbee-dialogue to fix problems introduced with an earlier commit 24 Dec 2014 that wasn't completed.
2016-03-09 Update of AP mode test utility for latest libxbee installed and QT5 Still not working.
2016-03-20 Node example add more microcontroller outputs to match test board and allow for LED feedback.
2016-03-20 Update test board schematics and add an external serial version
2016-03-25 Minor documentation changes.
2016-03-27 Change atmega48 node to shift analogue input to AD2 on XBee away from commissioning button.
2016-03-29 XBee-node-test: correct PC interrupt initialization settings
2016-03-31 Minor changes to xbee-node-test after (futile) attempts to resolve a problem.
2016-04-02 Add new directory with wrapper for testing remote node firmware code on POSIX
2016-04-03 Xbee-node-test: Remove redundancies and make global variables static.
2016-04-03 xbee-node-test-pc: add in timer emulation and ISR from test code.
2016-04-05 xbee-node-test-pc: fix problem of serial port being accessed by serial.cpp. Also change function names in serial.c and serial.cpp so that getch is non-blocking.
2016-04-07 Remove old versions of watermeter PCB
2016-04-09 Major new version of the PCBs for next stage of production run.
2016-04-14 Some changes to design notes.
2016-04-14 xbee-node: fix problems with WDT interrupt and initialisation. Set working for ATMega48
2016-04-16 XBee-node-test: Start tests with the full node firmware.
2016-04-19 XBee-node-test: More corrections to serial getch to handle QTs API Pull debug statements from mainprog Add more debug statements to acqcontrol. Minor documentation changes
2016-04-23 XBee-firmware: Corrections to logic. Tested with good reception and lost ACK only so far. XBee-node-test-pc: extensive debug statements provided.
2016-04-25 In XBee-acqcontrol Add a transmission of a packet outside of protocol just before ACK
2016-04-25 Further correction to XBee-acqcontrol. The data length of the count data message is 10, but it cannot be derived from the message length reported by xbeelib3 since the acknowledge message arrives aft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
2016-04-30 Minor changes to firmware to network protocol to add an S command representing status message not received.
2016-05-06 Update to network flow diagram to add protocol response to errored status from the base station. Some additional clarification in the firmware.
2016-05-19 Update to Kicad PCB files to slightly adjust components and footprints to accomodate purchased materials.
2016-05-20 Updated pdfs of the PCBs. Photos of physical mockup.
2016-06-16 Addition of PCB layout to testboard with footprints taken mainly from Kicad GitHub repository. Not yet routed
2016-06-18 Bedug interface board modify to add mounting holes.
2016-11-14 Update of Main PCB and generation of gerbers.
2016-11-14 Update of Mounts boards PCBs and generation of gerbers.
2016-12-05 Minor corrections to testboard schematic
2016-12-07 Rename of firmware-test to count-test in Development directory.
2016-12-08 Change makefiles to point to installed avr-gcc. Corrections to READMEs Small change to (abandoned) Xbee-firmware-nartos to account for a move to another directory (but it still doesn't compile).
2016-12-23 Correct an error that stopped the GUI setting debug mode.
2017-01-06 Add power jumper to disconnect testboard power from meter when battery is present in the latter.
2017-01-07 Update to xbee-node-test to remove some global variable use in the receiver routines. This has a bug to be fixed. Add code to check for the XBee in association before moving on to the main loop. This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
2017-01-11 Update firmware to reflect library changes.
2017-01-13 XBee-node-test-pc: some mods to prevent program catching in an endless loop if a bad message was received.
2017-01-13 Libraries: Move defines out into defines.h header file.
2017-01-14 XBee-firmware: change names of files to reflect directory. Attempts to have the firmware working with sleep modes is not successful.
2017-01-14 Xbee-firmware: enable hardware flow control, re-enable sleep for the AVR and remove delays arounf test pin
2017-01-14 Enable flow control in test firmware.
2017-01-16 Fix error in acqcontrol to interpret I/O sample correctly
2017-01-18 Update Main board PCB to modify battery monitor circuit.
2017-01-18 Minor mods to PCB for kicad Testboard
2017-01-20 XBee-acqcontrol: separate out processing for data messages that do not follow the error correction protocol. Ensure that all messages are stored to file.
2017-01-24 Minor change to Kicad-Mounts to remove dependence on rescue.lib
2017-01-26 Add a test-sleep module to the Xbee-node-test-pc.
2017-01-28 Change some names in the structs used to define XBee AP packets to match those used in the XBee documentation.
2017-01-30 Kicad-Main, Kicad-Mounts and Kicad-Testboard. Add a range of symbol and footprint libraries and repair some problems apparently due to randomized changes in Kicad repository libraries.
2017-01-31 Kicad-Xbee-node-test: first draft of PCB
2017-02-01 Xbee-node-test-sleep. Fix bug with VBAT_CON. Add compile options to choose whether to sleep MCU, XBee and make battery measurement.
2017-02-02 Minor tweaks on the PCBs ready to manufacture
2017-02-04 Rework Xbee-node-test-pc to put in an option for C language emulator. Test programs changed to use printf rather than QT functions. QT emulator extended to activate combo boxes correctly.
2017-02-06 The Xbee-node-test-pc emulator is expanded to provide a c code emulator, avoiding the qt5 environment needed. This is useful for running on small devices such as the Raspberry Pi or BeagleBone that m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
2017-02-07 Correct error in XBee-node-test-pc emulator-c that didn't register a different serial port command line setting. More messages in mainprog-firmware. Update to README
2017-02-11 Resolve issue between old version of CAM350 (9.5) and latest gerber format 4.6 where circles were not rendered correctly.
2017-02-24 Modifications to XBee-node-test-pc firmware to reset XBee on failure and to add further debug printing.
2017-02-26 Correct some stupid errors in Testboard and XBee-node-test PCBs.
2017-03-01 Main board PCB: generation of extra gerber layers
2017-03-02 Update XBee symbol in node-test and mounts PCB schematics.
2017-03-06 Serial board prototype: add ground to RTS on XBee in case RTS is enabled. This line left open could pull low.
2017-03-06 Correct error in xbee-libs in which association indication query was testing the wrong field. This fixes a problem in which the query always returned zero prematurely.
2017-03-12 Xbee-node-test-pc: added time printout to mainprog and update time delay computations.
2017-03-14 Update design and test notes
2017-03-17 Firmware update to 1.2. Shift packet error enum to xbee.h for global access.
2017-03-20 Xbee-node-test-pc emulator-c. Add file logging and correct error in which serial read() was partially blocking. VTIME should be 0.
2017-03-22 Remove some auxiliary Kicad backup files.
2017-03-30 acqcontrol: close any open connections for a node when ID arrives. This is intended to tackle problem of network failure when nodes experience trouble and restart their XBee. Move Transmit Status con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
2017-04-05 Modify firmware to add a delay to prevent the AVR from sleeping while counts are changing. Fix arithmetic problem in acqcontrol to display counts correctly.
2017-05-05 Minor fix to allow display of processed count/voltage values.
2017-05-26 Acqcontrol: rearrangement of network command action code to match the documentation ordering.
2017-05-27 GUI major rearrangement of code to pull out some common functions.
2017-06-02 Start development of a command interface for the sleeping XBees. Responds to stayawake command changes but still rather hit and miss. Doesn't always receive the message.
2017-06-08 Serial interrupt test to verify that interrupts work. Transmit ok but while receive works it is sporadic. Doesn't seem to be buffering, something in the reception of serial characters. Was tested on 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
2017-06-12 Firmware: make command line protocol more general. Emulator: bring up to date with firmware changes. GUI: change tool tips on node config and adapt to new protocol.
2017-12-02 Correct error in logging that caused program failure when logging was not enabled. Update documents.

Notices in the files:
Development/XBee-node-test-pc/mainprog-test-sleep.cpp:
Copyright (C) 2016 by Ken Sarkies (www.jiggerjuice.info)
Licensed under the Apache License, Version 2.0 (the "License");
XBee-bootloader-M168/bootloader.c:
Copyright (C) 2013 by Ken Sarkies ksarkies@internode.on.net
